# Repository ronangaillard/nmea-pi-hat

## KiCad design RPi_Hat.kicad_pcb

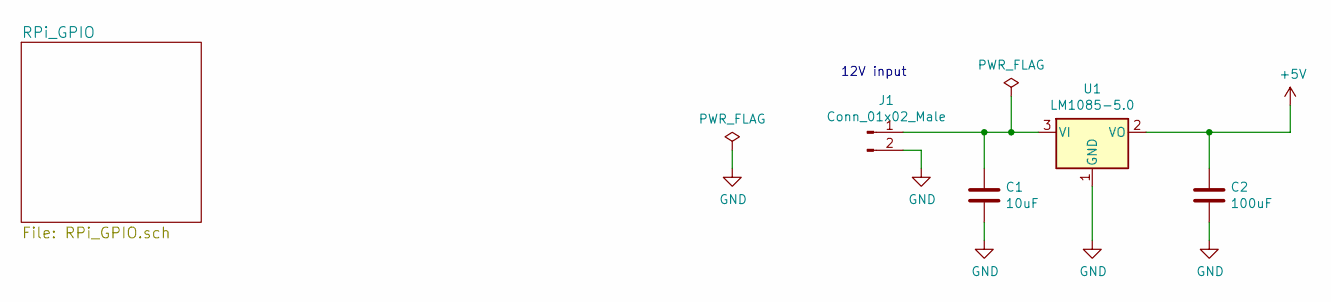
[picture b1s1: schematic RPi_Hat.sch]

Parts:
C1: 10uF; L_0805_HandSoldering
C2: 100uF; C_1206_HandSoldering
J1: Conn_01x02_Male; JST_SH_SM02B-SRSS-TB_02x1.00mm_Angled
U1: LM1085-5.0; TO-263-3_TabPin2

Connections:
+5V: C2.1, U1.2 (VO); also elsewhere on the board
GND: C1.2, C2.2, J1.2, U1.1 (GND); also elsewhere on the board
unnamed: C1.1, J1.1, U1.3 (VI)

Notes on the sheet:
12V input

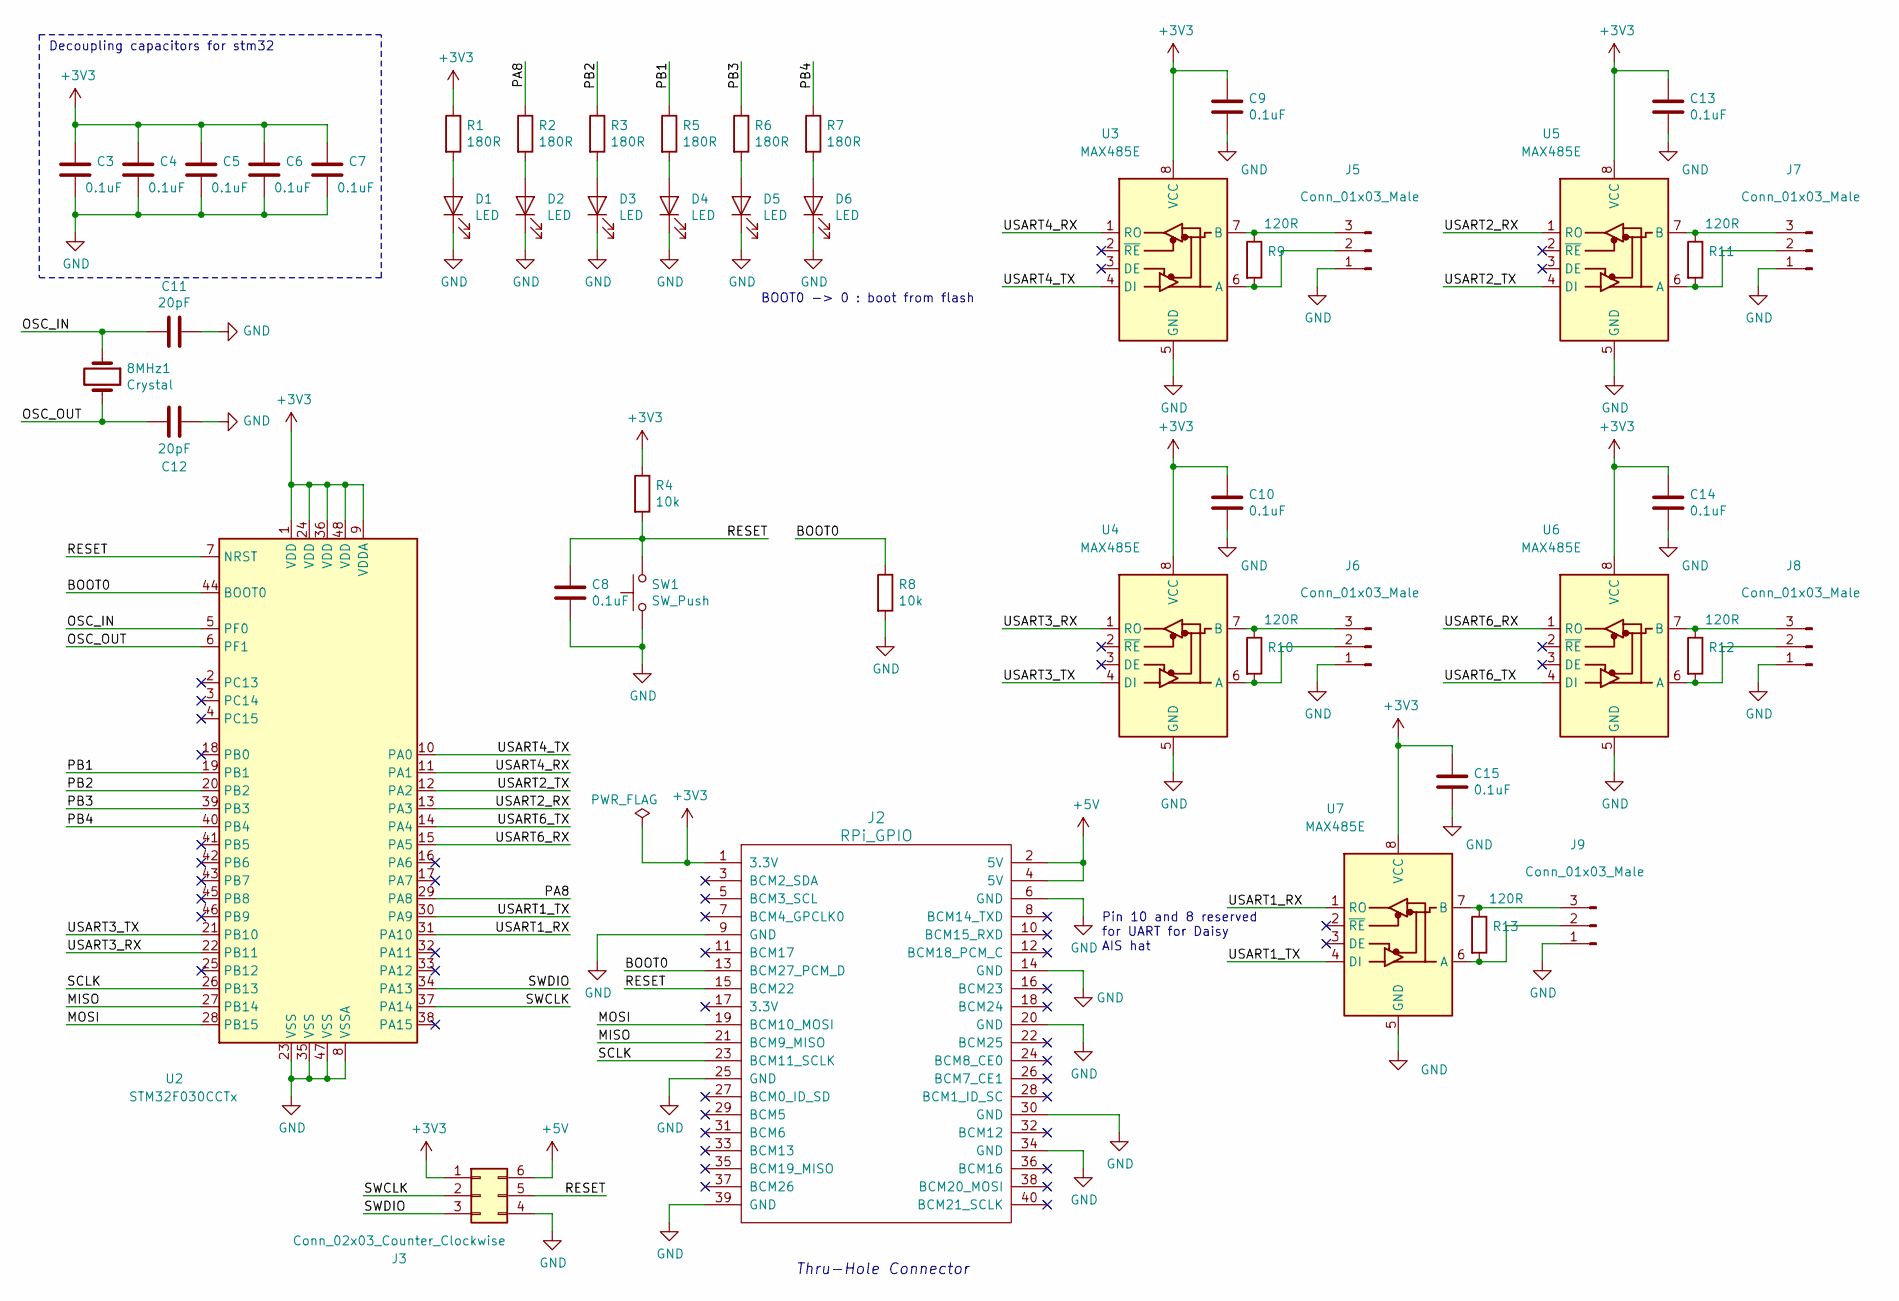
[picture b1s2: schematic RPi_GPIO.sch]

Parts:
8MHz1: Crystal; Crystal_SMD_HC49-SD_HandSoldering
C3, C4, C5, C6, C7, C8, C9, C10, C13, C14, C15: 0.1uF; C_0603_HandSoldering
C11, C12: 20pF; C_0603_HandSoldering
D1, D2, D3, D4, D5, D6: LED; LED_0603_HandSoldering
J2: RPi_GPIO; Pin_Header_Straight_2x20
J3: Conn_02x03_Counter_Clockwise; SDL-106-X-XX_2x03
J5, J6, J7, J8, J9: Conn_01x03_Male; JST_SH_SM03B-SRSS-TB_03x1.00mm_Angled
R1, R2, R3, R5, R6, R7: 180R; R_0603_HandSoldering
R4, R8: 10k; R_0603_HandSoldering
R9, R10, R11, R12, R13: 120R; R_0603_HandSoldering
SW1: SW_Push; Switch_Tactile_SMD_6x6mm
U2: STM32F030CCTx; LQFP-48_7x7mm
U3, U4, U5, U6, U7: MAX485E; SOIC-8_W3.9mm

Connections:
+3V3: C3.1, C4.1, C5.1, C6.1, C7.1, C9.1, C10.1, C13.1, C14.1, C15.1, J2.1 (3.3V), J3.1, R1.1, R4.1, U2.1 (VDD), U2.9 (VDDA), U2.24 (VDD), U2.36 (VDD), U2.48 (VDD), U3.8 (VCC), U4.8 (VCC), U5.8 (VCC), U6.8 (VCC), U7.8 (VCC)
+5V: J2.2 (5V), J2.4 (5V), J3.6; also elsewhere on the board
/RPi_GPIO/BOOT0: J2.13 (BCM27_PCM_D), R8.1, U2.44 (BOOT0)
/RPi_GPIO/MISO: J2.21 (BCM9_MISO), U2.27 (PB14)
/RPi_GPIO/MOSI: J2.19 (BCM10_MOSI), U2.28 (PB15)
/RPi_GPIO/OSC_IN: 8MHz1.1, C11.2, U2.5 (PF0)
/RPi_GPIO/OSC_OUT: 8MHz1.2, C12.2, U2.6 (PF1)
/RPi_GPIO/PA8: R2.1, U2.29 (PA8)
/RPi_GPIO/PB1: R5.1, U2.19 (PB1)
/RPi_GPIO/PB2: R3.1, U2.20 (PB2)
/RPi_GPIO/PB3: R6.1, U2.39 (PB3)
/RPi_GPIO/PB4: R7.1, U2.40 (PB4)
/RPi_GPIO/RESET: C8.1, J2.15 (BCM22), J3.5, R4.2, SW1.2, U2.7 (NRST)
/RPi_GPIO/SCLK: J2.23 (BCM11_SCLK), U2.26 (PB13)
/RPi_GPIO/SWCLK: J3.2, U2.37 (PA14)
/RPi_GPIO/SWDIO: J3.3, U2.34 (PA13)
/RPi_GPIO/USART1_RX: U2.31 (PA10), U7.1 (RO)
/RPi_GPIO/USART1_TX: U2.30 (PA9), U7.4 (DI)
/RPi_GPIO/USART2_RX: U2.13 (PA3), U5.1 (RO)
/RPi_GPIO/USART2_TX: U2.12 (PA2), U5.4 (DI)
/RPi_GPIO/USART3_RX: U2.22 (PB11), U4.1 (RO)
/RPi_GPIO/USART3_TX: U2.21 (PB10), U4.4 (DI)
/RPi_GPIO/USART4_RX: U2.11 (PA1), U3.1 (RO)
/RPi_GPIO/USART4_TX: U2.10 (PA0), U3.4 (DI)
/RPi_GPIO/USART6_RX: U2.15 (PA5), U6.1 (RO)
/RPi_GPIO/USART6_TX: U2.14 (PA4), U6.4 (DI)
GND: C3.2, C4.2, C5.2, C6.2, C7.2, C8.2, C9.2, C10.2, C11.1, C12.1, C13.2, C14.2, C15.2, D1.1 (K), D2.1 (K), D3.1 (K), D4.1 (K), D5.1 (K), D6.1 (K), J2.6 (GND), J2.9 (GND), J2.14 (GND), J2.20 (GND), J2.25 (GND), J2.30 (GND), J2.34 (GND), J2.39 (GND), J3.4, J5.1, J6.1, J7.1, J8.1, J9.1, R8.2, SW1.1, U2.8 (VSSA), U2.23 (VSS), U2.35 (VSS), U2.47 (VSS), U3.5 (GND), U4.5 (GND), U5.5 (GND), U6.5 (GND), U7.5 (GND); also elsewhere on the board
unnamed: D1.2 (A), R1.2
unnamed: D2.2 (A), R2.2
unnamed: D3.2 (A), R3.2
unnamed: D4.2 (A), R5.2
unnamed: D5.2 (A), R6.2
unnamed: D6.2 (A), R7.2
unnamed: J5.2, R9.2, U3.6 (A)
unnamed: J5.3, R9.1, U3.7 (B)
unnamed: J6.2, R10.2, U4.6 (A)
unnamed: J6.3, R10.1, U4.7 (B)
unnamed: J7.2, R11.2, U5.6 (A)
unnamed: J7.3, R11.1, U5.7 (B)
unnamed: J8.2, R12.2, U6.6 (A)
unnamed: J8.3, R12.1, U6.7 (B)
unnamed: J9.2, R13.2, U7.6 (A)
unnamed: J9.3, R13.1, U7.7 (B)

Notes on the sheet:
Thru-Hole Connector
Decoupling capacitors for stm32
BOOT0 -> 0 : boot from flash
Pin 10 and 8 reserved for UART for Daisy AIS hat

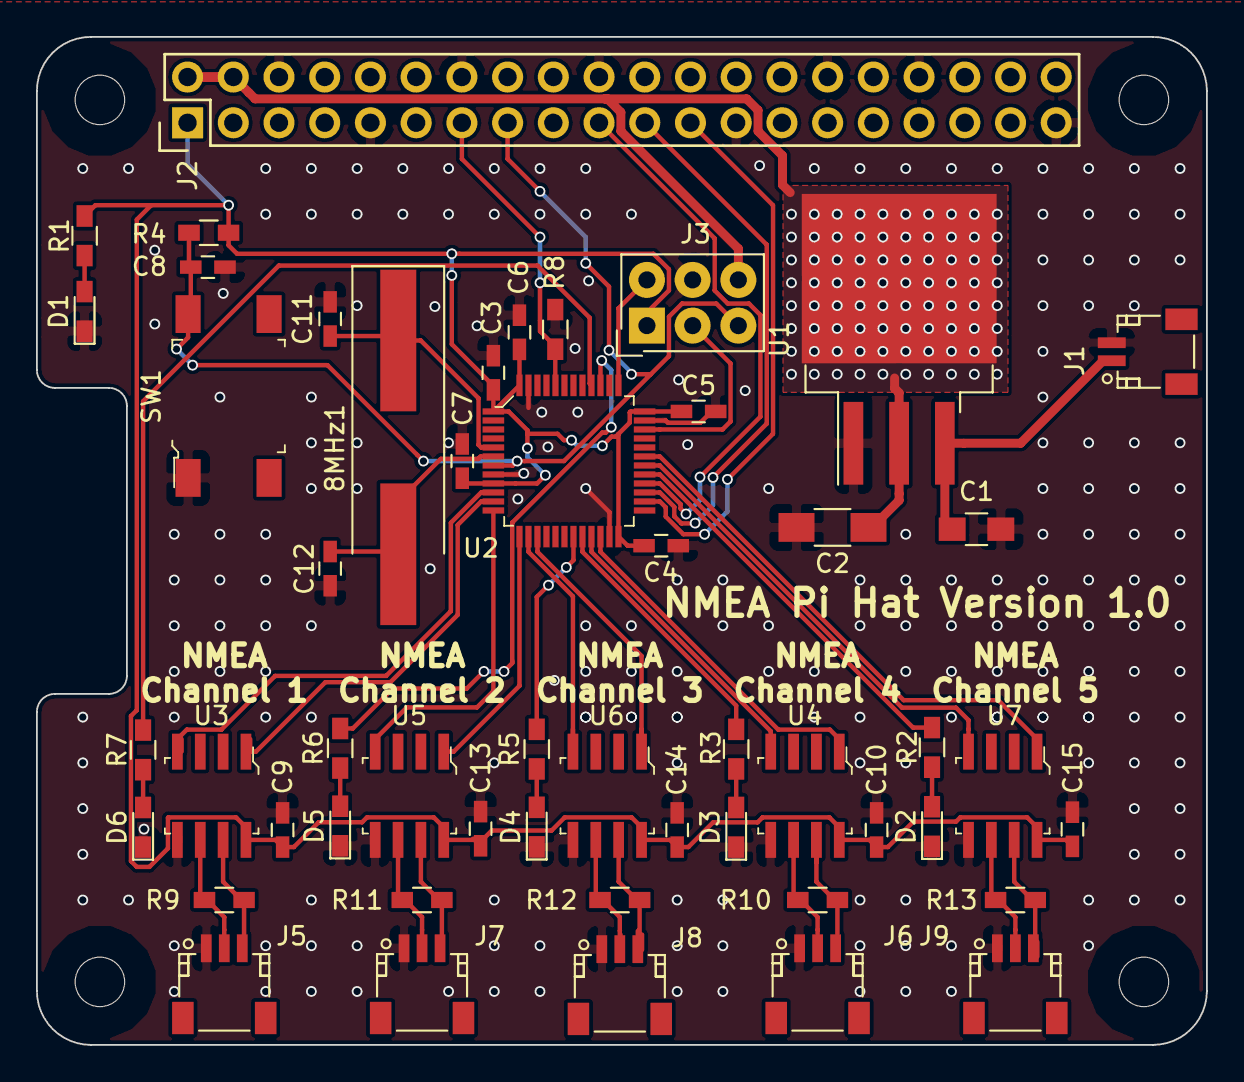
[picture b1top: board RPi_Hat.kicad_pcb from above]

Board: 2 copper layers, 65.0 x 56.0 mm, 51 parts (0 on the bottom side), 44 nets.

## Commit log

2019-01-23 Update files for KiCad 5
2019-01-23 Update files to use through hole connecotr
2019-01-24 First ver of schems
2019-01-24 Improve schems
2019-01-24 Start to fill components footprints and dkRef
2019-01-29 Change components ref and package
2019-01-29 Correct DRC and add nmea interface
2019-01-30 Finish schem and start routing
2019-01-30 Place all components on board
2019-02-08 Update footprints, fix gnd missing, start to align connectors
2019-02-08 Keepon routing
2019-02-09 Finished routing
2019-02-10 Add silkscreen info
2019-02-10 Connect reset and boot0 to raspi and change few things
2019-02-10 Add some vias
2019-02-10 Add termination resistors in schematics
2019-02-10 Add terminaison resistors
